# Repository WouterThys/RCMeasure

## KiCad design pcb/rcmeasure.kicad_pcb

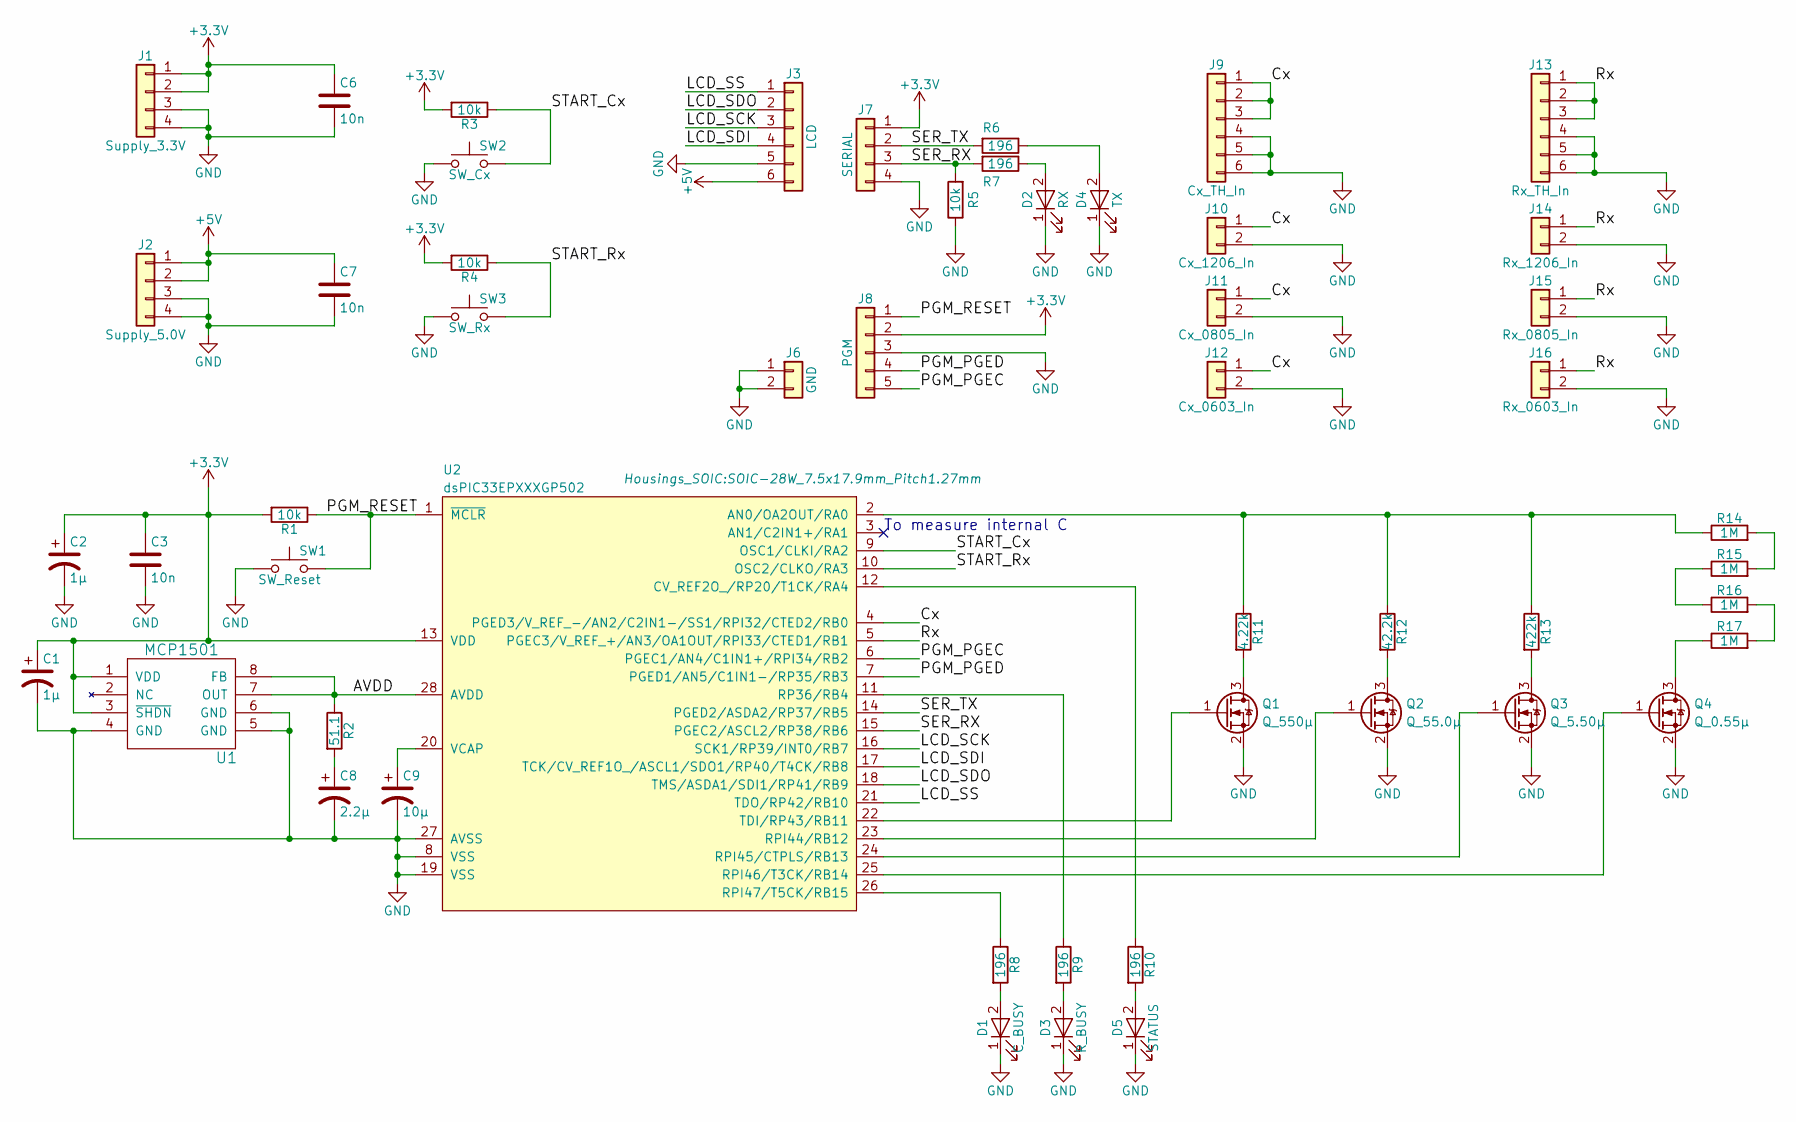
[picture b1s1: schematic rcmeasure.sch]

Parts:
C1, C2: 1µ; C_0603_HandSoldering
C3, C6, C7: 10n; C_0603_HandSoldering
C8: 2.2µ; CP_Tantalum_Case-A_EIA-3216-18_Hand
C9: 10µ; CP_Tantalum_Case-A_EIA-3216-18_Hand
D1: C_BUSY; LED_0603_HandSoldering
D2: RX; LED_0603_HandSoldering
D3: R_BUSY; LED_0603_HandSoldering
D4: TX; LED_0603_HandSoldering
D5: STATUS; LED_0603_HandSoldering
J1: Supply_3.3V; Molex_PicoBlade_53047-0410_04x1.25mm_Straight
J2: Supply_5.0V; Molex_PicoBlade_53047-0410_04x1.25mm_Straight
J3: LCD; Molex_PicoBlade_53047-0610_06x1.25mm_Straight
J6: GND; Pin_Header_Straight_1x02_Pitch2.54mm
J7: SERIAL; Molex_PicoBlade_53047-0410_04x1.25mm_Straight
J8: PGM; Pin_Header_Angled_1x05_Pitch2.54mm
J9: Cx_TH_In; Pin_Header_Straight_1x06_Pitch2.54mm
J10: Cx_1206_In; CP_Tantalum_Case-A_EIA-3216-18_Hand
J11: Cx_0805_In; C_0805_HandSoldering
J12: Cx_0603_In; C_0603_HandSoldering
J13: Rx_TH_In; Pin_Header_Straight_1x06_Pitch2.54mm
J14: Rx_1206_In; R_1206_HandSoldering
J15: Rx_0805_In; R_0805_HandSoldering
J16: Rx_0603_In; R_0603_HandSoldering
Q1: Q_550µ; SOT-23_Handsoldering
Q2: Q_55.0µ; SOT-23_Handsoldering
Q3: Q_5.50µ; SOT-23_Handsoldering
Q4: Q_0.55µ; SOT-23_Handsoldering
R1, R3, R4, R5: 10k; R_0603_HandSoldering
R2: 51.1; R_0603_HandSoldering
R6, R7, R8, R9, R10: 196; R_0603_HandSoldering
R11: 4.22k; R_0603_HandSoldering
R12: 42.2k; R_0603_HandSoldering
R13: 422k; R_0603_HandSoldering
R14, R15, R16, R17: 1M; R_0603_HandSoldering
SW1: SW_Reset; SW_SPST_B3S-1000
SW2: SW_Cx; SW_SPST_B3S-1000
SW3: SW_Rx; SW_SPST_B3S-1000
U1: MCP1501; SOIC-8_3.9x4.9mm_Pitch1.27mm
U2: dsPIC33EPXXXGP502; SOIC-28W_7.5x17.9mm_Pitch1.27mm

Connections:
+3V3: C1.1, C2.1, C3.1, C6.1, J1.1, J1.2, J7.1, J8.2, R1.2, R3.2, R4.2, U1.1 (VDD), U1.3 (~SHDN), U2.13 (VDD)
+5V: C7.1, J2.1, J2.2, J3.6
/AVDD: R2.1, U1.7 (OUT), U1.8 (FB), U2.28 (AVDD)
/Cx: J9.1, J9.2, J9.3, J10.1, J11.1, J12.1, U2.4 (PGED3/V_REF_-/AN2/C2IN1-/SS1/RPI32/CTED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)
/LCD_SCK: J3.3, U2.16 (SCK1/RP39/INT0/RB7)
/LCD_SDI: J3.4, U2.17 (TCK/CV_REF1O_/ASCL1/SDO1/RP40/T4CK/RB8)
/LCD_SDO: J3.2, U2.18 (TMS/ASDA1/SDI1/RP41/RB9)
/LCD_SS: J3.1, U2.21 (TDO/RP42/RB10)
/PGM_PGEC: J8.5, U2.6 (PGEC1/AN4/C1IN1+/RPI34/RB2)
/PGM_PGED: J8.4, U2.7 (PGED1/AN5/C1IN1-/RP35/RB3)
/PGM_RESET: J8.1, R1.1, SW1.2, U2.1 (~MCLR)
/Rx: J13.1, J13.2, J13.3, J14.1, J15.1, J16.1, U2.5 (PGEC3/V_REF_+/AN3/OA1OUT/RPI33/CTED1/RB1)
/SER_RX: J7.3, R5.2, R7.2, U2.15 (PGEC2/ASCL2/RP38/RB6)
/SER_TX: J7.2, R6.2, U2.14 (PGED2/ASDA2/RP37/RB5)
/START_Cx: R3.1, SW2.2, U2.9 (OSC1/CLKI/RA2)
/START_Rx: R4.1, SW3.2, U2.10 (OSC2/CLKO/RA3)
GND: C1.2, C2.2, C3.2, C6.2, C7.2, C8.2, C9.2, D1.1 (K), D2.1 (K), D3.1 (K), D4.1 (K), D5.1 (K), J1.3, J1.4, J2.3, J2.4, J3.5, J6.1, J6.2, J7.4, J8.3, J9.4, J9.5, J9.6, J10.2, J11.2, J12.2, J13.4, J13.5, J13.6, J14.2, J15.2, J16.2, Q1.2 (S), Q2.2 (S), Q3.2 (S), Q4.2 (S), R5.1, SW1.1, SW2.1, SW3.1, U1.4 (GND), U1.5 (GND), U1.6 (GND), U2.8 (VSS), U2.19 (VSS), U2.27 (AVSS)
unnamed: C8.1, R2.2
unnamed: C9.1, U2.20 (VCAP)
unnamed: D1.2 (A), R8.2
unnamed: D2.2 (A), R7.1
unnamed: D3.2 (A), R9.2
unnamed: D4.2 (A), R6.1
unnamed: D5.2 (A), R10.2
unnamed: Q1.1 (G), U2.22 (TDI/RP43/RB11)
unnamed: Q1.3 (D), R11.2
unnamed: Q2.1 (G), U2.23 (RPI44/RB12)
unnamed: Q2.3 (D), R12.2
unnamed: Q3.1 (G), U2.24 (RPI45/CTPLS/RB13)
unnamed: Q3.3 (D), R13.2
unnamed: Q4.1 (G), U2.25 (RPI46/T3CK/RB14)
unnamed: Q4.3 (D), R17.1
unnamed: R8.1, U2.26 (RPI47/T5CK/RB15)
unnamed: R9.1, U2.11 (RP36/RB4)
unnamed: R10.1, U2.12 (CV_REF2O_/RP20/T1CK/RA4)
unnamed: R11.1, R12.1, R13.1, R14.1, U2.2 (AN0/OA2OUT/RA0)
unnamed: R14.2, R15.2
unnamed: R15.1, R16.1
unnamed: R16.2, R17.2

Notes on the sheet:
To measure internal C

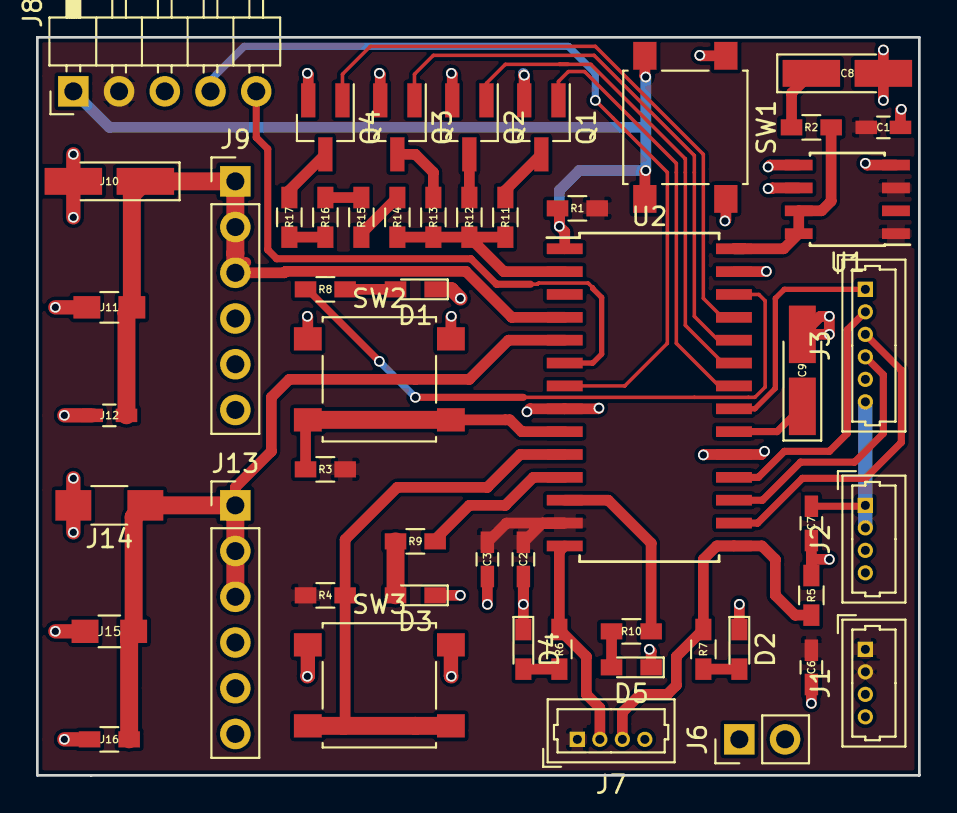
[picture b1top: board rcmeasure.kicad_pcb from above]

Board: 2 copper layers, 49.0 x 41.0 mm, 52 parts (0 on the bottom side), 39 nets.

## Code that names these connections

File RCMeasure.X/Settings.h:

/* 
 * File:   
 * Author: 
 * Comments:
 * Revision history: 
 */

// This is a guard condition so that contents of this file are not included
// more than once.  
#ifndef SETTINGS_H
#define	SETTINGS_H

#include <xc.h> // include processor files - each processor file is guarded.  


#define DEBUG       1


/**
 * Interrupt priorities
 */

#define CN_IP       2     
#define T2_IP       1  
#define U1RX_IP     3
    
/**
 *  PIC
 */
 
#define LED1            PORTBbits.RB15
#define LED1_Dir        TRISBbits.TRISB15
#define LED2            PORTBbits.RB14
#define LED2_Dir        TRISBbits.TRISB14
    
/**
 * UART
 */      
#define UART1_BAUD      57600
#define UART1_ID        2   

#define UART1_RX_Dir    TRISBbits.TRISB6    /* RX Pin on RP38-RB6             */
#define UART1_TX_Dir    TRISBbits.TRISB7    /* TX Pin on RP39-RB7             */

#define UART1_RX_Map    0b0100110           /* I/O RP38                       */
#define UART1_TX_Map    0b000001


/**
 * CTMU
 */
#define CTMU_MODE_EDGE  0

#define RANGE_0_55uA    1       /* Base current = 0.55 µA                     */
#define RANGE_5_50uA    2       /* 10x base current = 5.5µA                   */
#define RANGE_55_0uA    3       /* 100x base current = 55µA                   */
#define RANGE_550_uA    0       /* 1000x base current = 550µA                 */

#define RCAL_0_55uA     3.9e6   /* R 3.9M for 0.55µA source                   */
#define RCAL_5_50uA     390e3   /* R 390k for 5.50µA source                   */
#define RCAL_55_0uA     39e3    /* R  39k for 55µA source                     */
#define RCAL_550uA      3.9e3   /* R 3.9k for 550µA source                    */

/**
 * Delay: calculated with C V = I t. 
 *  - C = guess for internal system C (around 40pF)
 *  - V = 70% of ADREF
 *  - I = ideal value for range
 */

#define DELAY_0_55uA    167    /* Delay 167µs for 0.55µA source               */
#define DELAY_5_50uA    17     /* Delay  17µs for 5.50µA source               */
#define DELAY_55_0uA    1      /* Delay   1µ for 55µA source                  */
#define DELAY_550uA     1      /* Delay   1µ for 550µA source                 */

#define PORT_0_55uA     LATBbits.LATB13
#define PORT_5_50uA     LATBbits.LATB12
#define PORT_55_0uA     LATBbits.LATB11
#define PORT_550uA      LATBbits.LATB10

#define ADSCALE         1023    /* 10-bit ADC, 1023                           */
#define ADREF           3.3     /* Vref is 3.3V                               */

#define IIT_CALIBRATE   10      /* Number of iterations  for calibration      */
#define IIT_MAX         500     /* Max number of iterations when measuring C  */
#define DELAY_STEP      20      /* Steps per delay iteration                  */      
#define DELAY_MAX       5e3     /* Max delay for a selected source range      */
#define DELAY_MIN       20      /* Min delay for a selected source range      */
    

#endif	/* XC_HEADER_TEMPLATE_H */

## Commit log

2018-01-25 created current iteration test
2018-01-26 strange stuff
2018-02-04 create pcb and clean up c code
2018-02-04 resistance measurement
